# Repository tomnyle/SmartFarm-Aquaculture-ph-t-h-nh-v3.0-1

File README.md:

# SmartFarm Aquaculture Controller V0.3

ESP32-based aquaculture controller for family pond management with MQTT & Home Assistant integration.

## Features

- **Autonomous Control**: Works independently even without Home Assistant
- **Multi-Species Support**: Profiles for Koi, Catfish, Shrimp, Tilapia, and more
- **4 Operating Modes**: AUTO, MANUAL, SCHEDULE, SAFE
- **Safe Runtime Operation Profiles**: `SENSOR_TEST`, `NO_LIVESTOCK_TEST`, and `PRODUCTION`
- **Commissioning Interlocks**: Separate `can_no_load_test`, `can_production`, retained block reasons, and livestock confirmation
- **Core Sensors**:
  - Water Temperature (DS18B20)
  - pH Level (via ADS1115)
  - Dissolved Oxygen (via ADS1115)
  - Turbidity

- **Relay Control** (8-channel):
  - Aerator (Máy sục khí)
  - Water Pump (Bơm cấp nước)
  - Circulation Pump (Bơm tuần hoàn)
  - Feeder (Máy cho ăn)
  - Valve (Van)
  - Light (Đèn)
  - 2x Spare

## Hardware Requirements

- 30-pin ESP32 DevKit (select the exact module footprint before PCB layout)
- DS18B20 Temperature Sensor
- pH Electrode + ADS1115 ADC Module
- Dissolved Oxygen Probe + ADS1115
- Water Level Sensor
- 8-Channel Relay Module
- 5V Power Supply

See [`docs/hardware.md`](docs/hardware.md) for the PCB-A/PCB-B layout plan, pin mapping,
and requirements for using a purchased 8-channel relay module. Matched board-level
specifications and the PCB-A/PCB-B connector pinout are in [`hardware/`](hardware/).

## Getting Started

### 1. Clone Repository
```bash
git clone https://github.com/tomnyle/SmartFarm-Aquaculture.git
cd SmartFarm-Aquaculture
```

### 2. Configure
Edit `include/app_config.h`:
- WiFi SSID & Password
- MQTT Broker Address
- Device Name & Location
- `SENSOR_TEST_MODE` (keep `true` until commissioning is complete)

### 3. Build & Upload
```bash
platformio run -e esp32dev -t upload
```

### 4. Monitor Serial Output
```bash
platformio device monitor -b 115200
```

## System Architecture

```
         Home Assistant
              │
             MQTT
              │
      Aquaculture ESP32
              │
    ┌─────────┼─────────┐
    │         │         │
Sensors  Rule Engine  Outputs
    │         │         │
    └─────────┼─────────┘
         Local Controller
```

## Operating Modes

### AUTO Mode
ESP32 automatically controls relays based on sensor readings and active profile thresholds.

### MANUAL Mode
Control relays directly from Home Assistant.

### SCHEDULE Mode
Execute predefined schedules (e.g., feeding times).

### SAFE Mode
Activated when critical errors detected:
- Sensor failures
- Water level too low
- Temperature critical
- DO critical

## Operation Profile State Machine

The firmware now keeps a second safety layer for commissioning and production selection:

- `SENSOR_TEST`
  - Sensor-only validation.
  - Outputs stay locked OFF.
  - ON commands are suppressed.
  - AUTO rules are skipped.
- `NO_LIVESTOCK_TEST`
  - Wet / no-load test with no animals.
  - Allowed only when:
    - required sensors are valid (`water_temp`, `pH`, `DO`, `turbidity`)
    - no required sensor fault is active
    - `SENSOR_TEST_MODE=false`
    - no critical condition is active
    - no external output lock is active (currently `SAFE` mode)
    - relay test status is `PASSED`
- `PRODUCTION`
  - Real livestock production.
  - Requires everything from `NO_LIVESTOCK_TEST`, plus:
    - retained `livestock_present=ON`
    - no active alarm is present

Runtime note:

- `SENSOR_TEST_MODE` is its own blocker and always forces the active profile back to `SENSOR_TEST`.
- The active `SENSOR_TEST` profile still locks outputs at runtime, but that profile lock is not reused as an eligibility blocker when evaluating whether the next requested profile can be accepted.

Requested profile changes from Home Assistant are never trusted blindly:

- Unsafe `NO_LIVESTOCK_TEST` requests are downgraded to `SENSOR_TEST`.
- Unsafe `PRODUCTION` requests are downgraded to the safest valid profile:
  - `PRODUCTION` when fully eligible
  - otherwise `NO_LIVESTOCK_TEST` when commissioning-safe
  - otherwise `SENSOR_TEST`

Stable blocker codes published by the firmware:

- `required_sensor_invalid`
- `sensor_fault_active`
- `relay_test_not_passed`
- `outputs_locked`
- `sensor_test_mode_enabled`
- `active_alarm`
- `livestock_not_confirmed`
- `critical_condition_active`

## Profiles

Each species has predefined parameter ranges:

```json
{
  "name": "shrimp",
  "temperature": { "min": 28, "max": 32 },
  "ph": { "min": 7.5, "max": 8.5 },
  "do": { "min": 5.0 }
}
```

## MQTT Topics

Core retained topics:

- `smartfarm/aquaculture/sensor/*` - Sensor readings
- `smartfarm/aquaculture/output/*` - Output states
- `smartfarm/aquaculture/config/mode/set|state`
- `smartfarm/aquaculture/config/species/set|state`
- `smartfarm/aquaculture/config/operation_profile/set|selected|actual`
- `smartfarm/aquaculture/config/livestock_present/set|state`
- `smartfarm/aquaculture/config/relay_test/set|requested|state`
- `smartfarm/aquaculture/eligibility/can_no_load_test`
- `smartfarm/aquaculture/eligibility/can_production`
- `smartfarm/aquaculture/eligibility/outputs_locked`
- `smartfarm/aquaculture/eligibility/required_sensors_valid`
- `smartfarm/aquaculture/eligibility/sensor_fault_active`
- `smartfarm/aquaculture/eligibility/any_active_alarm`
- `smartfarm/aquaculture/eligibility/critical_condition_active`
- `smartfarm/aquaculture/eligibility/block_reason_codes`
- `smartfarm/aquaculture/eligibility/block_reason_summary`
- `smartfarm/aquaculture/eligibility/production_block_reason`
- `smartfarm/aquaculture/eligibility/active_reminder`
- `smartfarm/aquaculture/eligibility/blockers/*`

Home Assistant MQTT discovery also creates entities for:

- operation profile selector
- active profile sensor
- livestock present switch
- relay test request selector and status sensor
- can no-load test
- can production
- outputs locked
- production block reason / active reminder
- per-blocker reminder indicators

Binary-sensor style eligibility and blocker topics publish retained `ON` / `OFF` payloads. Select entities publish fixed option strings such as `SENSOR_TEST`, `NO_LIVESTOCK_TEST`, `PRODUCTION`, `NOT_STARTED`, `IN_PROGRESS`, `PASSED`, and `FAILED`.

## Home Assistant Automation Example

Example persistent notification when a requested profile is rejected or the active block reason changes:

```yaml
automation:
  - alias: Aquaculture profile blocked
    trigger:
      - platform: state
        entity_id:
          - sensor.aquaculture_operation_profile_block_summary
          - sensor.aquaculture_active_profile
    condition:
      - condition: template
        value_template: >
          {{ states('sensor.aquaculture_operation_profile_block_summary') not in
             ['All profile conditions satisfied', 'unknown', 'unavailable'] }}
    action:
      - service: persistent_notification.create
        data:
          title: Aquaculture profile reminder
          message: >
            Requested={{ states('select.aquaculture_operation_profile') }}
            Actual={{ states('sensor.aquaculture_active_profile') }}
            Summary={{ states('sensor.aquaculture_operation_profile_block_summary') }}
```

## Documentation

See `/docs` folder for:
- `architecture.md` - System design
- `hardware.md` - PCB-A/PCB-B KiCad projects and relay module requirements
- `sensors.md` - Sensor specifications & calibration
- `wiring.md` - Hardware wiring diagram
- `mqtt.md` - MQTT protocol details

Open the KiCad designs with KiCad 10 (files use the KiCad 9 file format):
- [`hardware/pcb-a/pcb-a.kicad_pro`](hardware/pcb-a/pcb-a.kicad_pro)
- [`hardware/pcb-b/pcb-b.kicad_pro`](hardware/pcb-b/pcb-b.kicad_pro)

The current PCB layouts are unrouted starting points and are not ready for fabrication;
see [`docs/hardware.md`](docs/hardware.md) before assembling or ordering boards.

## License

MIT License - See LICENSE file

## Author

Tom Nyle (tomnyle) - 2026

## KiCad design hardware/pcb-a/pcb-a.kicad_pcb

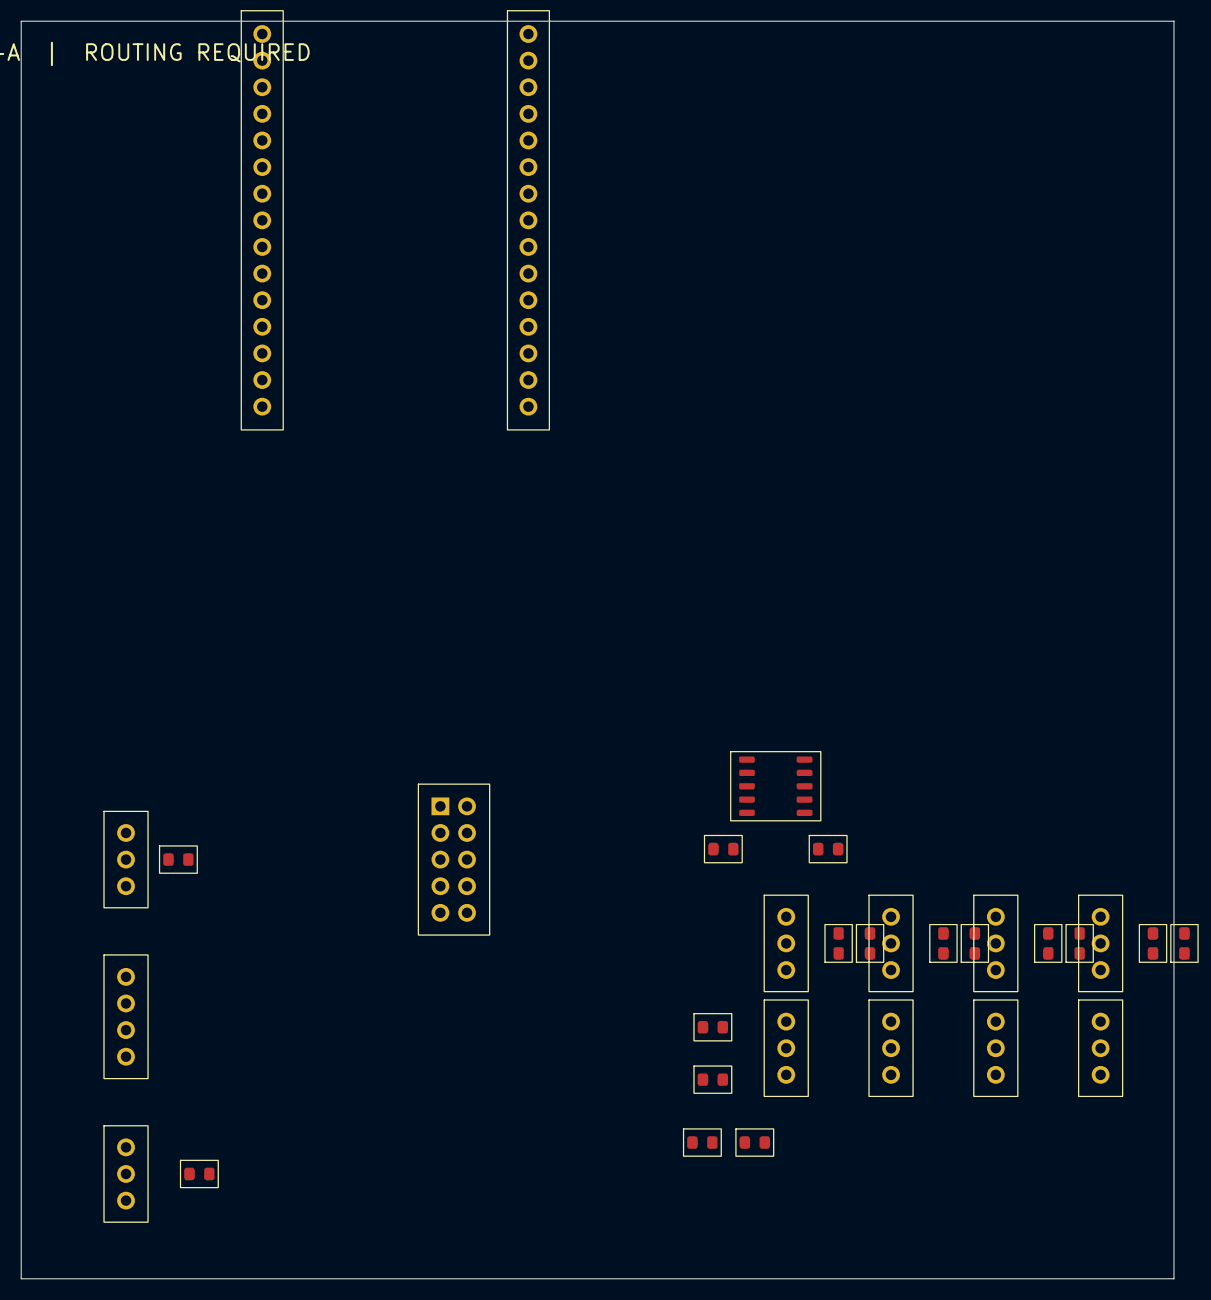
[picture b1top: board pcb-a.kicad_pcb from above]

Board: 2 copper layers, 110.0 x 120.0 mm, 31 parts (0 on the bottom side), 28 nets, no tracks yet.

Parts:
C1: 100nF; SF_C_0603
C2: 10uF; SF_C_0603
D1: Status LED; SF_LED_0603
J1: ESP32 socket left row; SF_PinSocket_1x15
J2: ESP32 socket right row; SF_PinSocket_1x15
J3: PH sensor; SF_PinHeader_1x3
J4: DO sensor; SF_PinHeader_1x3
J5: TURB sensor; SF_PinHeader_1x3
J6: CO2 sensor; SF_PinHeader_1x3
J7: DS18B20; SF_PinHeader_1x3
J8: I2C expansion; SF_PinHeader_1x4
J9: PCB-B relay connector; SF_PinHeader_2x5
J10: DHT22; SF_PinHeader_1x3
JP1, JP2, JP3, JP4: 3V3/5V sensor supply; SF_Jumper_3
R1, R3, R5, R7: 12k; SF_R_0603
R2, R4, R6, R8: 20k; SF_R_0603
R9, R13: 4.7k pull-up; SF_R_0603
R10, R11: 4.7k; SF_R_0603
R12: 1k LED; SF_R_0603
U1: ADS1115; SF_SOIC10

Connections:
3V3: C1.1, C2.1, J1.1, J7.1, J8.1, J10.1, JP1.1, JP2.1, JP3.1, JP4.1, R9.1, R10.1, R11.1, R13.1, U1.8
5V_VIN: J2.1, JP1.3, JP2.3, JP3.3, JP4.3
CO2_ADC: R7.2, R8.1, U1.7
CO2_RAW: J6.3, R7.1
CO2_VCC: J6.1, JP4.2
DHT22_DATA: J1.3, J10.2, R13.2
DO_ADC: R3.2, R4.1, U1.5
DO_RAW: J4.3, R3.1
DO_VCC: J4.1, JP2.2
DS18B20_DATA: J1.5, J7.2, R9.2
GND: C1.2, C2.2, D1.1, J1.2, J2.2, J3.2, J4.2, J5.2, J6.2, J7.3, J8.2, J9.9, J9.10, J10.3, R2.2, R4.2, R6.2, R8.2, U1.1, U1.3
GPIO2: J1.4, R12.1
I2C_SCL: J1.14, J8.4, R11.2, U1.9
I2C_SDA: J1.11, J8.3, R10.2, U1.10
PH_ADC: R1.2, R2.1, U1.4
PH_RAW: J3.3, R1.1
PH_VCC: J3.1, JP1.2
RELAY1: J2.3, J9.1
RELAY2: J2.8, J9.2
RELAY3: J2.5, J9.3
RELAY4: J2.6, J9.4
RELAY5: J2.10, J9.5
RELAY6: J2.9, J9.6
RELAY8: J1.15, J9.8
STAT_LED_A: D1.2, R12.2
TURB_ADC: R5.2, R6.1, U1.6
TURB_RAW: J5.3, R5.1
TURB_VCC: J5.1, JP3.2

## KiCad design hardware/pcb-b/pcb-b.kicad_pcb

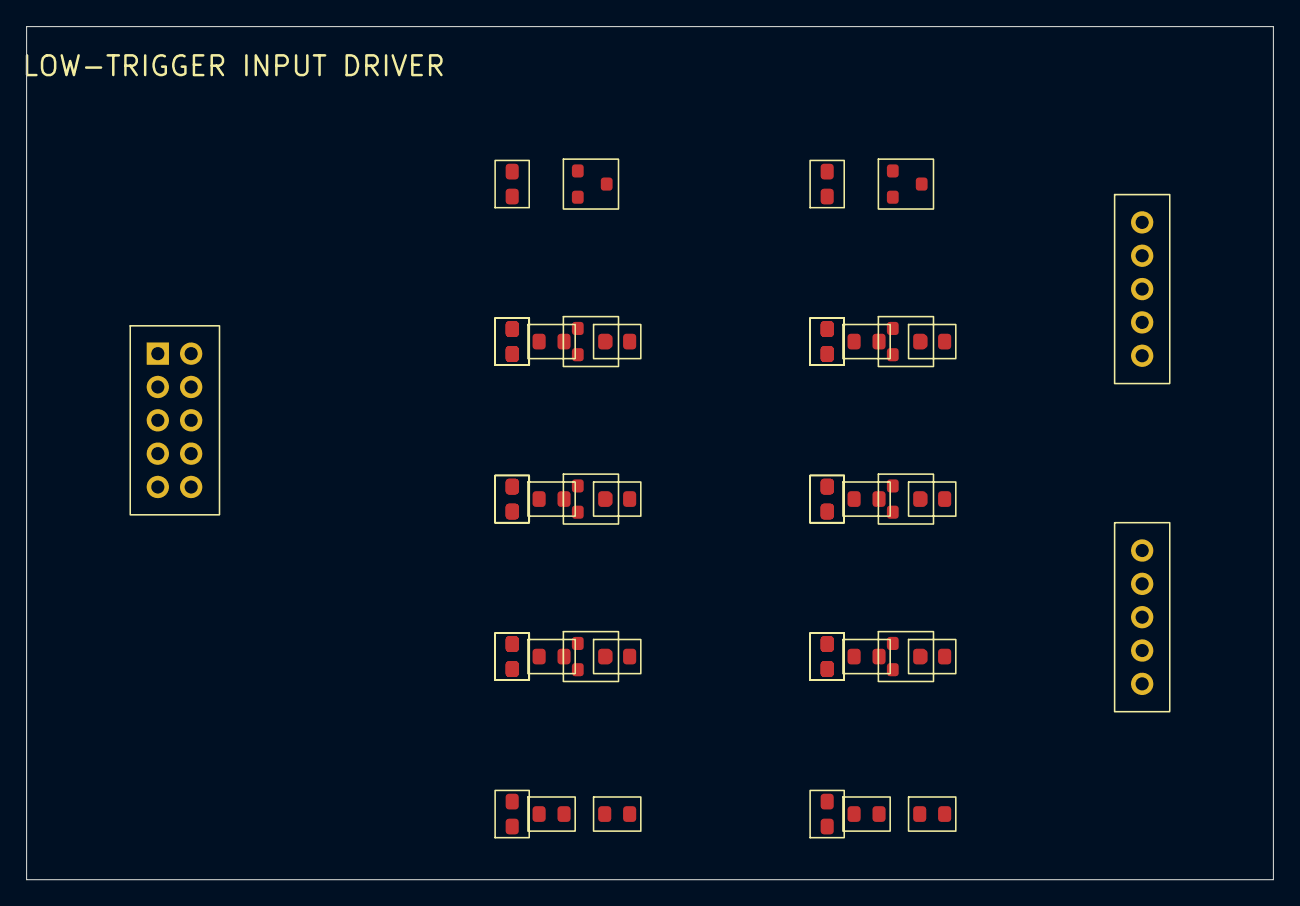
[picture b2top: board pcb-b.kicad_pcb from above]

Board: 2 copper layers, 95.0 x 65.0 mm, 43 parts (0 on the bottom side), 33 nets, no tracks yet.

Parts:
D1: CH1; SF_LED_0603
D2: CH2; SF_LED_0603
D3: CH3; SF_LED_0603
D4: CH4; SF_LED_0603
D5: CH5; SF_LED_0603
D6: CH6; SF_LED_0603
D7: CH7; SF_LED_0603
D8: CH8; SF_LED_0603
J1: PCB-A J_AB; SF_PinHeader_2x5
J2: Relay module input 1-4; SF_PinHeader_1x5
J3: Relay module input 5-8; SF_PinHeader_1x5
Q1, Q2, Q3, Q4, Q5, Q6, Q7, Q8: BC817-40; SF_SOT23
R1, R2, R3, R4, R5, R6, R7, R8: 2.2k base; SF_R_0603
R9, R10, R11, R12, R13, R14, R15, R16: 10k pulldown; SF_R_0603
R17, R18, R19, R20, R21, R22, R23, R24: 1k LED; SF_R_0603

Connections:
GND: D1.1, D2.1, D3.1, D4.1, D5.1, D6.1, D7.1, D8.1, J1.9, J1.10, J2.1, J3.1, Q1.2, Q2.2, Q3.2, Q4.2, Q5.2, Q6.2, Q7.2, Q8.2, R9.2, R10.2, R11.2, R12.2, R13.2, R14.2, R15.2, R16.2
LED1_A: D1.2, R17.2
LED2_A: D2.2, R18.2
LED3_A: D3.2, R19.2
LED4_A: D4.2, R20.2
LED5_A: D5.2, R21.2
LED6_A: D6.2, R22.2
LED7_A: D7.2, R23.2
LED8_A: D8.2, R24.2
Q1_B: Q1.1, R1.2, R9.1
Q2_B: Q2.1, R2.2, R10.1
Q3_B: Q3.1, R3.2, R11.1
Q4_B: Q4.1, R4.2, R12.1
Q5_B: Q5.1, R5.2, R13.1
Q6_B: Q6.1, R6.2, R14.1
Q7_B: Q7.1, R7.2, R15.1
Q8_B: Q8.1, R8.2, R16.1
RELAY1: J1.1, R1.1, R17.1
RELAY2: J1.2, R2.1, R18.1
RELAY3: J1.3, R3.1, R19.1
RELAY4: J1.4, R4.1, R20.1
RELAY5: J1.5, R5.1, R21.1
RELAY6: J1.6, R6.1, R22.1
RELAY7: J1.7, R7.1, R23.1
RELAY8: J1.8, R8.1, R24.1
RELAY_IN1: J2.2, Q1.3
RELAY_IN2: J2.3, Q2.3
RELAY_IN3: J2.4, Q3.3
RELAY_IN4: J2.5, Q4.3
RELAY_IN5: J3.2, Q5.3
RELAY_IN6: J3.3, Q6.3
RELAY_IN7: J3.4, Q7.3
RELAY_IN8: J3.5, Q8.3

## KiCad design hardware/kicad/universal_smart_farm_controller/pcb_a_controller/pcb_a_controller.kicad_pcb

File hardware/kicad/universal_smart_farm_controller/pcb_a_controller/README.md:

# PCB-A controller layout starter

Open `pcb_a_controller.kicad_pro` in **KiCad 9**, then open its schematic and
board (`pcb_a_controller.kicad_sch` / `.kicad_pcb`). This is a placement
template, **not a routed, ERC/DRC-approved or manufacture-ready design**.
It incorporates only the PCB-A schematic and signal references from the
directly related draft schematic work; it does not include PCB-B or mains.

The board has a provisional 130 × 100 mm outline (no mounting holes), 54
placed standard-library footprints grouped as power, ESP32/RF, analog, RS485
and board-edge headers, and assigned pad nets from the schematic. U1 faces
the top edge. Its antenna projects toward/outside that edge; the on-board
antenna courtyard strip (x=141–189 mm, y=115–121.2 mm) is a **both-copper-layer
rule-area keepout** prohibiting copper pours, tracks, vias and pads. It does
not prohibit footprints because it overlaps the ESP32 module itself: do not
place any *other* component there. Do not put an enclosure, cable or metal in
front of or under the antenna; check the ESP32-WROOM-32E module datasheet and
manufacturer clearance before fixing board dimensions. Neither the board
outline nor component locations are final mechanical specifications.

**Nothing is routed:** there are zero tracks and no copper pours. In
particular, do not route the TPS5430 switch/feedback loop, 12 V/5 V/3.3 V
rails, ground return, analog inputs or RS485 before selecting components and
reviewing current, EMI, transient protection and return paths. C12 (the
provisional 220 µF buck output capacitor) has **no selected package in the
source schematic** and is intentionally **not placed**. Choose a real part
with suitable voltage, ripple, ESR, footprint and polarity, assign its
footprint in the schematic, then use **Tools → Update PCB from Schematic**
with KiCad 9. Do not treat missing C12 as optional in a powered circuit.
The ADS1115 inputs are nominal 0–5 V via dividers, not field-protected.
The RS485 interface lacks verified field surge/bias design. USB-UART J4 pin
2 is a **3.3 V reference output**, never a power input.

## Connector orientation (viewed from the component/top side)

J1 is a vertical **shrouded 2×6 IDC header**, with pin 1 at the top-left
of its footprint near the board's top/right edge, pin 2 immediately to its
right, and successive rows numbered 3/4 through 11/12 toward the bottom.
The shroud notch is on the left. Use a keyed mating assembly with **pin 1
to PCB-B pin 1**; do not assume a straight ribbon or mirrored bottom-side
view preserves numbering. Check the mating connector, shroud and cable
orientation physically before powering. J1 supplies the controller only;
it must not carry PCB-B load return current.

| Header | Pin order (1 onward) |
| --- | --- |
| J1 | protected 12 V, GND, OUT1, OUT2, OUT3, OUT4, OUT5, OUT6, OUT7, OUT8, GND, GND |
| J2 DS18B20 | 3V3, DATA, GND |
| J3 bare DHT22 | 3V3, DATA, NC, GND |
| J4 external 3V3 UART | GND, 3V3 reference, ESP TX, ESP RX |
| J5–J8 A0–A3 | 5V, sensor signal, GND |
| J9 I2C | 3V3, SDA, SCL, GND |
| J19 RS485 | A, B, GND |

The single-row connectors' pin 1 is their square pad; check the physical
sensor's connector orientation and do not substitute a DHT22 module for the
bare four-pin device without checking its pinout. `../pin_map.csv` and
`../connector_summary.csv` define the intended GPIO and interboard mapping;
the existing firmware has DHT22/OUT2 and ADC-path differences and has **not**
been changed to match this board.

## Review before any fabrication

The imported schematic had its labels and no-connect markers vertically
reflected relative to actual KiCad symbol pin coordinates. Those positions
have been corrected in this copy (without changing the intended pin map);
the board's pad nets now match J1 pin 1 = protected 12 V, pins 2/11/12 =
GND, and OUT1–OUT8 = pins 3–10. Verify all pinouts, regulator feedback and
decoupling, component/package selections, antenna geometry, mating header,
clearances and mechanical fit in **KiCad 9**. Run schematic ERC, synchronize
the PCB, route/review it, then run PCB DRC. Do not generate fabrication
outputs until those checks and hardware safety review are complete.

The available environment had **KiCad CLI 7.0.11**, which loaded and exported
the board as SVG, and its board parser reloaded all 54 footprints, pad nets
and the keepout. KiCad 7 cannot perform ERC on this KiCad 9 schematic and
its CLI has no PCB DRC command. A KiCad 9 open/sync/ERC and final DRC
remain mandatory; no Gerbers or drill files are supplied.

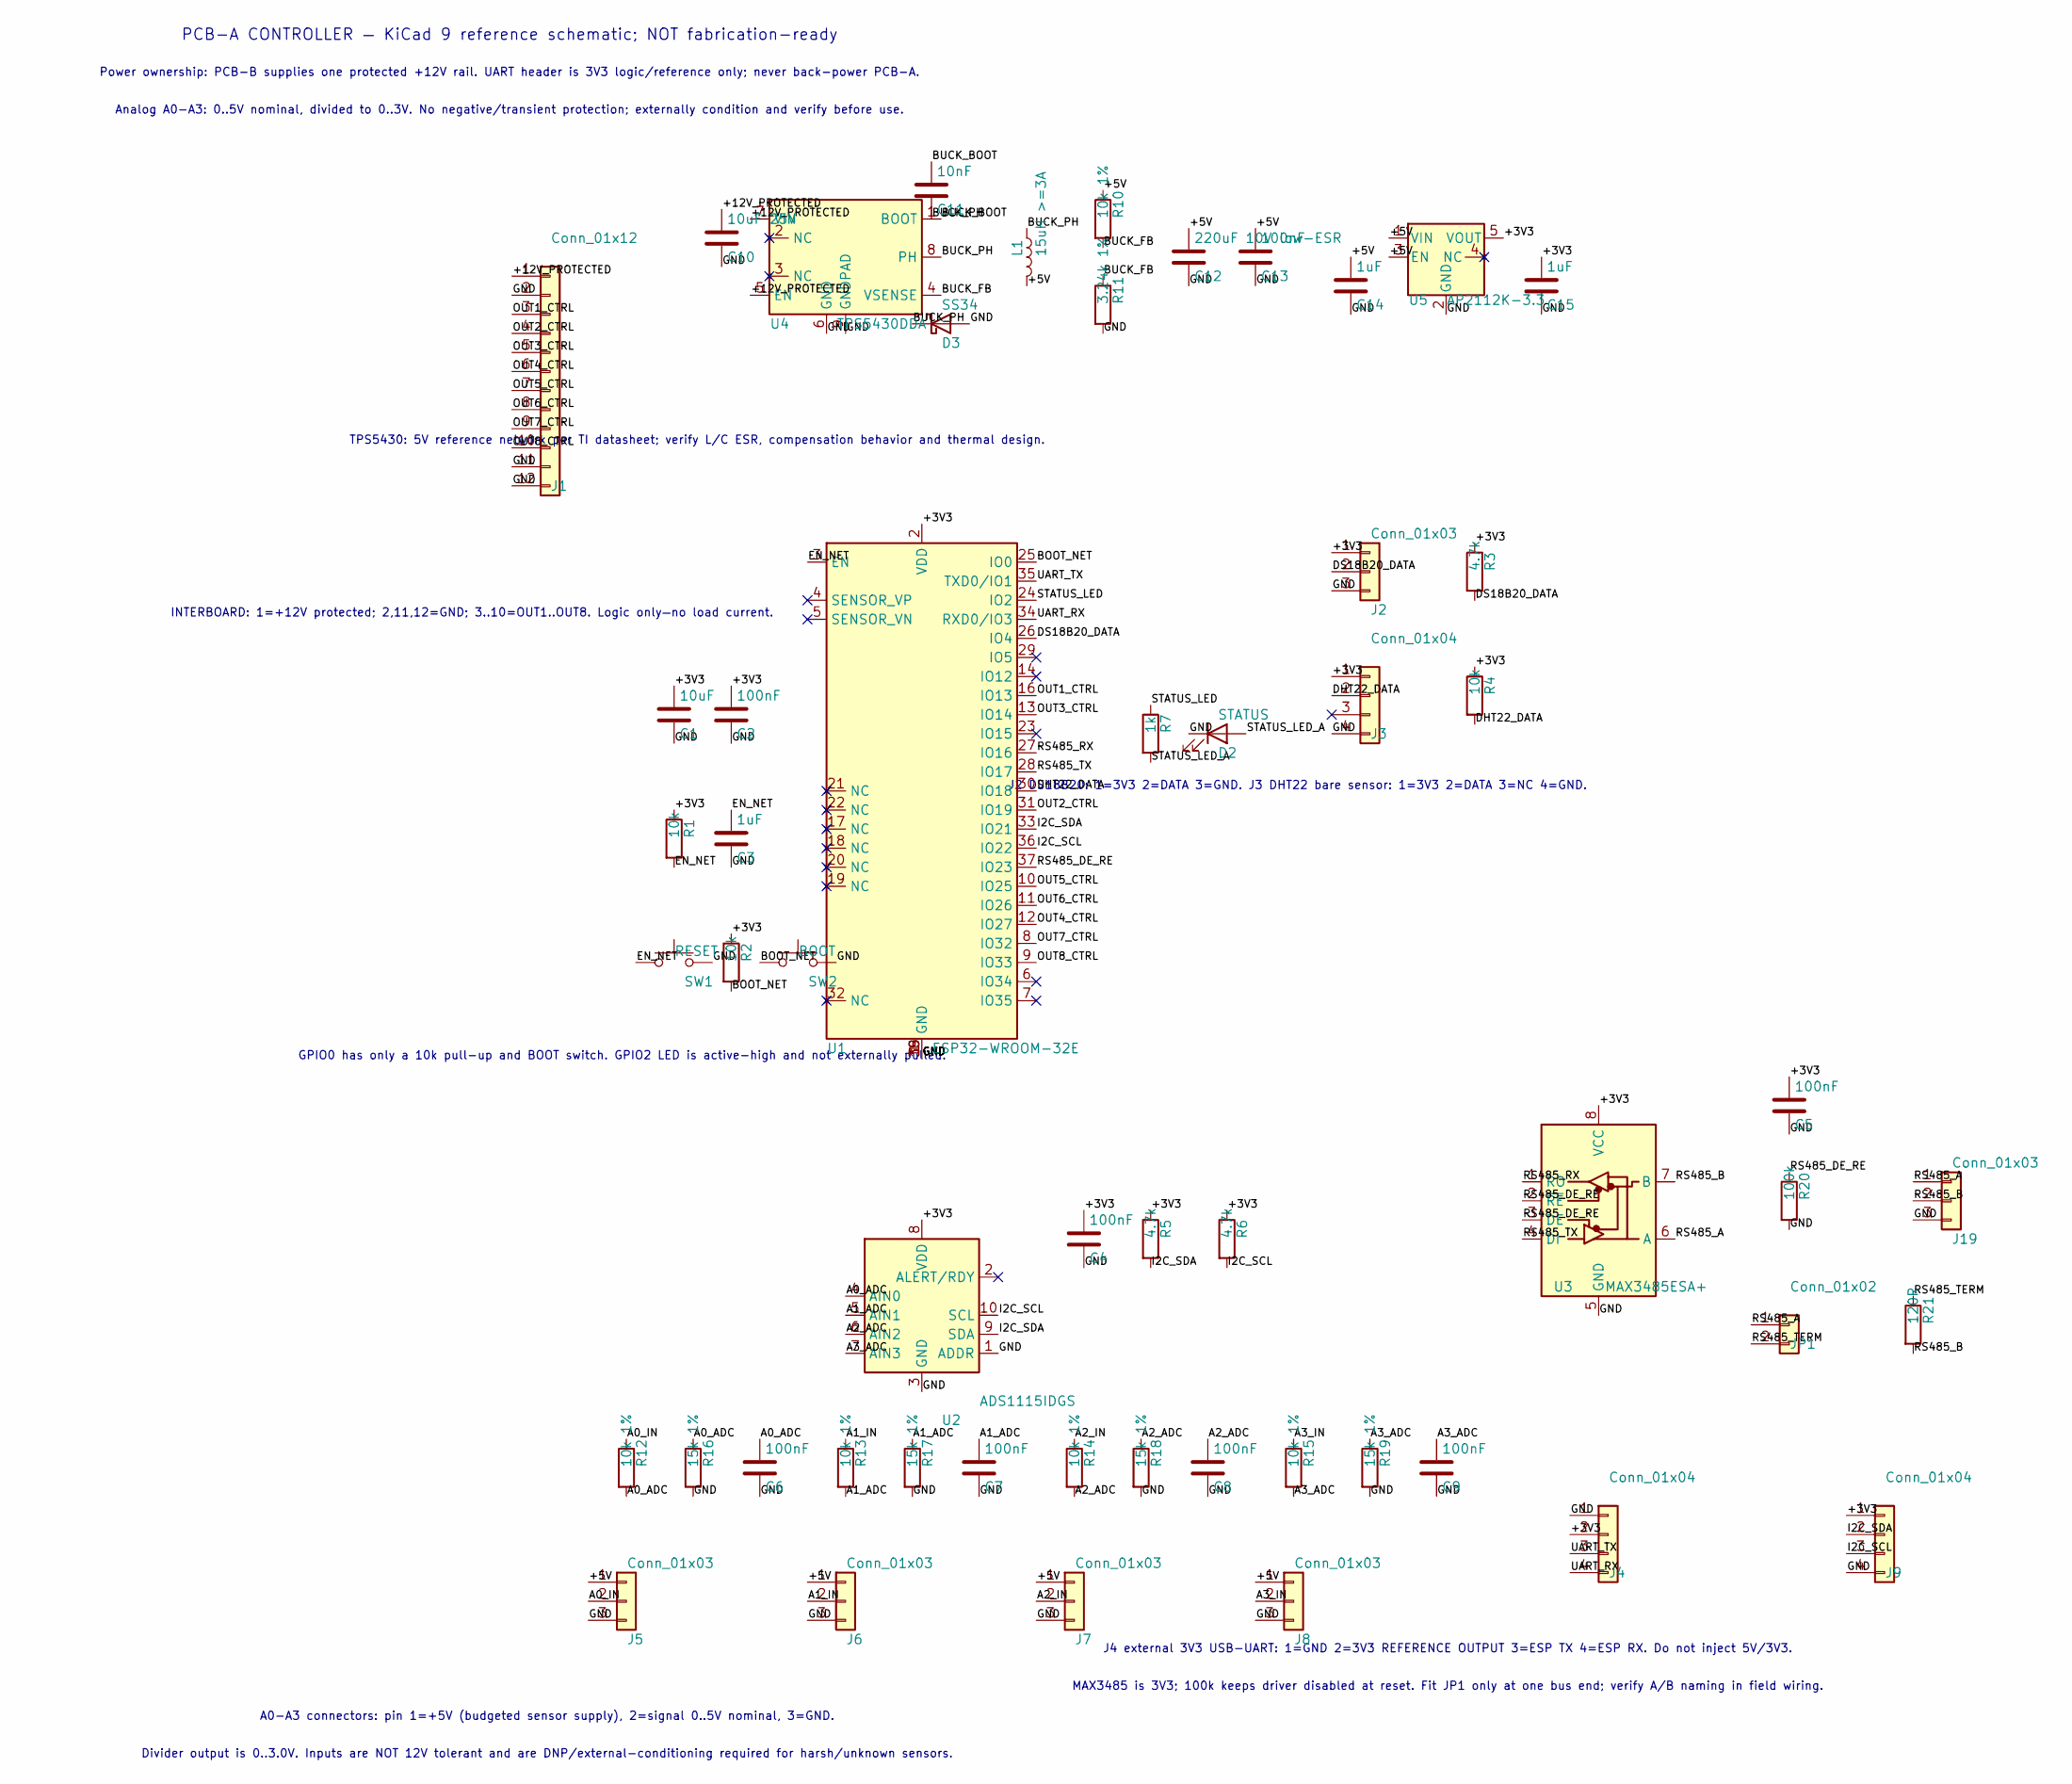
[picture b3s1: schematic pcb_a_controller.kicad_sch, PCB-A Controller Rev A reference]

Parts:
C1: 10uF; C_0805_2012Metric
C2, C4, C5, C6, C7, C8, C9, C13: 100nF; C_0805_2012Metric
C3, C14, C15: 1uF; C_0805_2012Metric
C10: 10uF 25V; C_0805_2012Metric
C11: 10nF; C_0805_2012Metric
C12: 220uF 10V low-ESR
D2: STATUS; LED_0805_2012Metric
D3: SS34; D_SMA
J1: Conn_01x12; IDC-Header_2x06_P2.54mm_Vertical
J2, J5, J6, J7, J8, J19: Conn_01x03; PinHeader_1x03_P2.54mm_Vertical
J3, J4, J9: Conn_01x04; PinHeader_1x04_P2.54mm_Vertical
JP1: Conn_01x02; PinHeader_1x02_P2.54mm_Vertical
L1: 15uH >=3A; L_1210_3225Metric_Pad1.42x2.65mm_HandSolder
R1, R2, R4: 10k; R_0805_2012Metric
R3, R5, R6: 4.7k; R_0805_2012Metric
R7: 1k; R_0805_2012Metric
R10, R12, R13, R14, R15: 10k 1%; R_0805_2012Metric
R11: 3.24k 1%; R_0805_2012Metric
R16, R17, R18, R19: 15k 1%; R_0805_2012Metric
R20: 100k; R_0805_2012Metric
R21: 120R; R_0805_2012Metric
SW1: RESET; SW_SPST_TL3342
SW2: BOOT; SW_SPST_TL3342
U1: ESP32-WROOM-32E; ESP32-WROOM-32
U2: ADS1115IDGS; VSSOP-10_3x3mm_P0.5mm
U3: MAX3485ESA+; SOIC-8_3.9x4.9mm_P1.27mm
U4: TPS5430DDA; Texas_HSOP-8-1EP_3.9x4.9mm_P1.27mm
U5: AP2112K-3.3; SOT-23-5

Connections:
+3V3: C1.1, C2.1, C4.1, C5.1, C15.1, J2.1, J3.1, J4.2, J9.1, R1.1, R2.1, R3.1, R4.1, R5.1, R6.1, U1.2 (VDD), U2.8 (VDD), U3.8 (VCC), U5.5 (VOUT)
+5V: C12.1, C13.1, C14.1, J5.1, J6.1, J7.1, J8.1, L1.2, R10.1, U5.1 (VIN), U5.3 (EN)
+12V_PROTECTED: C10.1, J1.1, U4.5 (EN), U4.7 (VIN)
A0_ADC: C6.1, R12.2, R16.1, U2.4 (AIN0)
A0_IN: J5.2, R12.1
A1_ADC: C7.1, R13.2, R17.1, U2.5 (AIN1)
A1_IN: J6.2, R13.1
A2_ADC: C8.1, R14.2, R18.1, U2.6 (AIN2)
A2_IN: J7.2, R14.1
A3_ADC: C9.1, R15.2, R19.1, U2.7 (AIN3)
A3_IN: J8.2, R15.1
BOOT_NET: R2.2, SW2.1, U1.25 (IO0)
BUCK_BOOT: C11.1, U4.1 (BOOT)
BUCK_FB: R10.2, R11.1, U4.4 (VSENSE)
BUCK_PH: C11.2, D3.1 (K), L1.1, U4.8 (PH)
DHT22_DATA: J3.2, R4.2, U1.30 (IO18)
DS18B20_DATA: J2.2, R3.2, U1.26 (IO4)
EN_NET: C3.1, R1.2, SW1.1, U1.3 (EN)
GND: C1.2, C2.2, C3.2, C4.2, C5.2, C6.2, C7.2, C8.2, C9.2, C10.2, C12.2, C13.2, C14.2, C15.2, D2.1 (K), D3.2 (A), J1.2, J1.11, J1.12, J2.3, J3.4, J4.1, J5.3, J6.3, J7.3, J8.3, J9.4, J19.3, R11.2, R16.2, R17.2, R18.2, R19.2, R20.2, SW1.2, SW2.2, U1.1 (GND), U1.15 (GND), U1.38 (GND), U1.39 (GND), U2.1 (ADDR), U2.3 (GND), U3.5 (GND), U4.6 (GND), U4.9 (GNDPAD), U5.2 (GND)
I2C_SCL: J9.3, R6.2, U1.36 (IO22), U2.10 (SCL)
I2C_SDA: J9.2, R5.2, U1.33 (IO21), U2.9 (SDA)
OUT1_CTRL: J1.3, U1.16 (IO13)
OUT2_CTRL: J1.4, U1.31 (IO19)
OUT3_CTRL: J1.5, U1.13 (IO14)
OUT4_CTRL: J1.6, U1.12 (IO27)
OUT5_CTRL: J1.7, U1.10 (IO25)
OUT6_CTRL: J1.8, U1.11 (IO26)
OUT7_CTRL: J1.9, U1.8 (IO32)
OUT8_CTRL: J1.10, U1.9 (IO33)
RS485_A: J19.1, JP1.1, U3.6 (A)
RS485_B: J19.2, R21.2, U3.7 (B)
RS485_DE_RE: R20.1, U1.37 (IO23), U3.2 (~RE), U3.3 (DE)
RS485_RX: U1.27 (IO16), U3.1 (RO)
RS485_TERM: JP1.2, R21.1
RS485_TX: U1.28 (IO17), U3.4 (DI)
STATUS_LED: R7.1, U1.24 (IO2)
STATUS_LED_A: D2.2 (A), R7.2
UART_RX: J4.4, U1.34 (RXD0/IO3)
UART_TX: J4.3, U1.35 (TXD0/IO1)

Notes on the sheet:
PCB-A CONTROLLER — KiCad 9 reference schematic; NOT fabrication-ready
Power ownership: PCB-B supplies one protected +12V rail. UART header is 3V3 logic/reference only; never back-power PCB-A.
Analog A0-A3: 0..5V nominal, divided to 0..3V. No negative/transient protection; externally condition and verify before use.
INTERBOARD: 1=+12V protected; 2,11,12=GND; 3..10=OUT1..OUT8. Logic only—no load current.
TPS5430: 5V reference network per TI datasheet; verify L/C ESR, compensation behavior and thermal design.
GPIO0 has only a 10k pull-up and BOOT switch. GPIO2 LED is active-high and not externally pulled.
J2 DS18B20: 1=3V3 2=DATA 3=GND. J3 DHT22 bare sensor: 1=3V3 2=DATA 3=NC 4=GND.
A0-A3 connectors: pin 1=+5V (budgeted sensor supply), 2=signal 0..5V nominal, 3=GND.
Divider output is 0..3.0V. Inputs are NOT 12V tolerant and are DNP/external-conditioning required for harsh/unknown sensors.
J4 external 3V3 USB-UART: 1=GND 2=3V3 REFERENCE OUTPUT 3=ESP TX 4=ESP RX. Do not inject 5V/3V3.
MAX3485 is 3V3; 100k keeps driver disabled at reset. Fit JP1 only at one bus end; verify A/B naming in field wiring.

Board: 2 copper layers, 54 parts (0 on the bottom side), 39 nets, no tracks yet.

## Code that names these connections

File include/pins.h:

#ifndef PINS_H
#define PINS_H

// ==================== SENSOR PINS ====================
// ADS1115 single-ended analog input channels
#define ADS1115_ADDRESS 0x48
#define PH_ADC_CHANNEL 0
#define DO_ADC_CHANNEL 1
#define TURBIDITY_ADC_CHANNEL 2
#define CO2_ADC_CHANNEL 3

// 1-Wire Bus
#define ONE_WIRE_BUS 4      // DS18B20 temperature sensor

// DHT Sensor
#define DHTPIN 15           // DHT22 data pin
#define DHTTYPE DHT22       // DHT22 sensor type

// I2C Pins (BH1750 Light Sensor)
#define I2C_SDA 21          // I2C Data
#define I2C_SCL 22          // I2C Clock

// ==================== OUTPUT PINS ====================
// Relay Pins
#define PUMP_PIN 13         // Main pump relay
#define AERATOR_PIN 25      // Aerator relay (GPIO12 is a boot-strapping pin)
#define CIRCULATION_PIN 14  // Circulation pump relay
#define FEEDER_PIN 27       // Automatic feeder relay
#define RELAY5_PIN 32       // Reserved relay output
#define RELAY6_PIN 33       // Reserved relay output
#define RELAY7_PIN 26       // Reserved relay output
#define RELAY8_PIN 23       // Reserved relay output

// Set RELAY_ACTIVE_LEVEL to LOW for active-low relay modules.
#ifndef RELAY_ACTIVE_LEVEL
#define RELAY_ACTIVE_LEVEL HIGH
#endif
#define RELAY_INACTIVE_LEVEL ((RELAY_ACTIVE_LEVEL) == HIGH ? LOW : HIGH)

// Status LED (Optional)
#define LED_PIN 2           // Built-in LED for status

// ==================== SPI PINS (Optional - Reserved) ====================
// #define SPI_MOSI 23
// #define SPI_MISO 19
// #define SPI_CLK 18

#endif // PINS_H
